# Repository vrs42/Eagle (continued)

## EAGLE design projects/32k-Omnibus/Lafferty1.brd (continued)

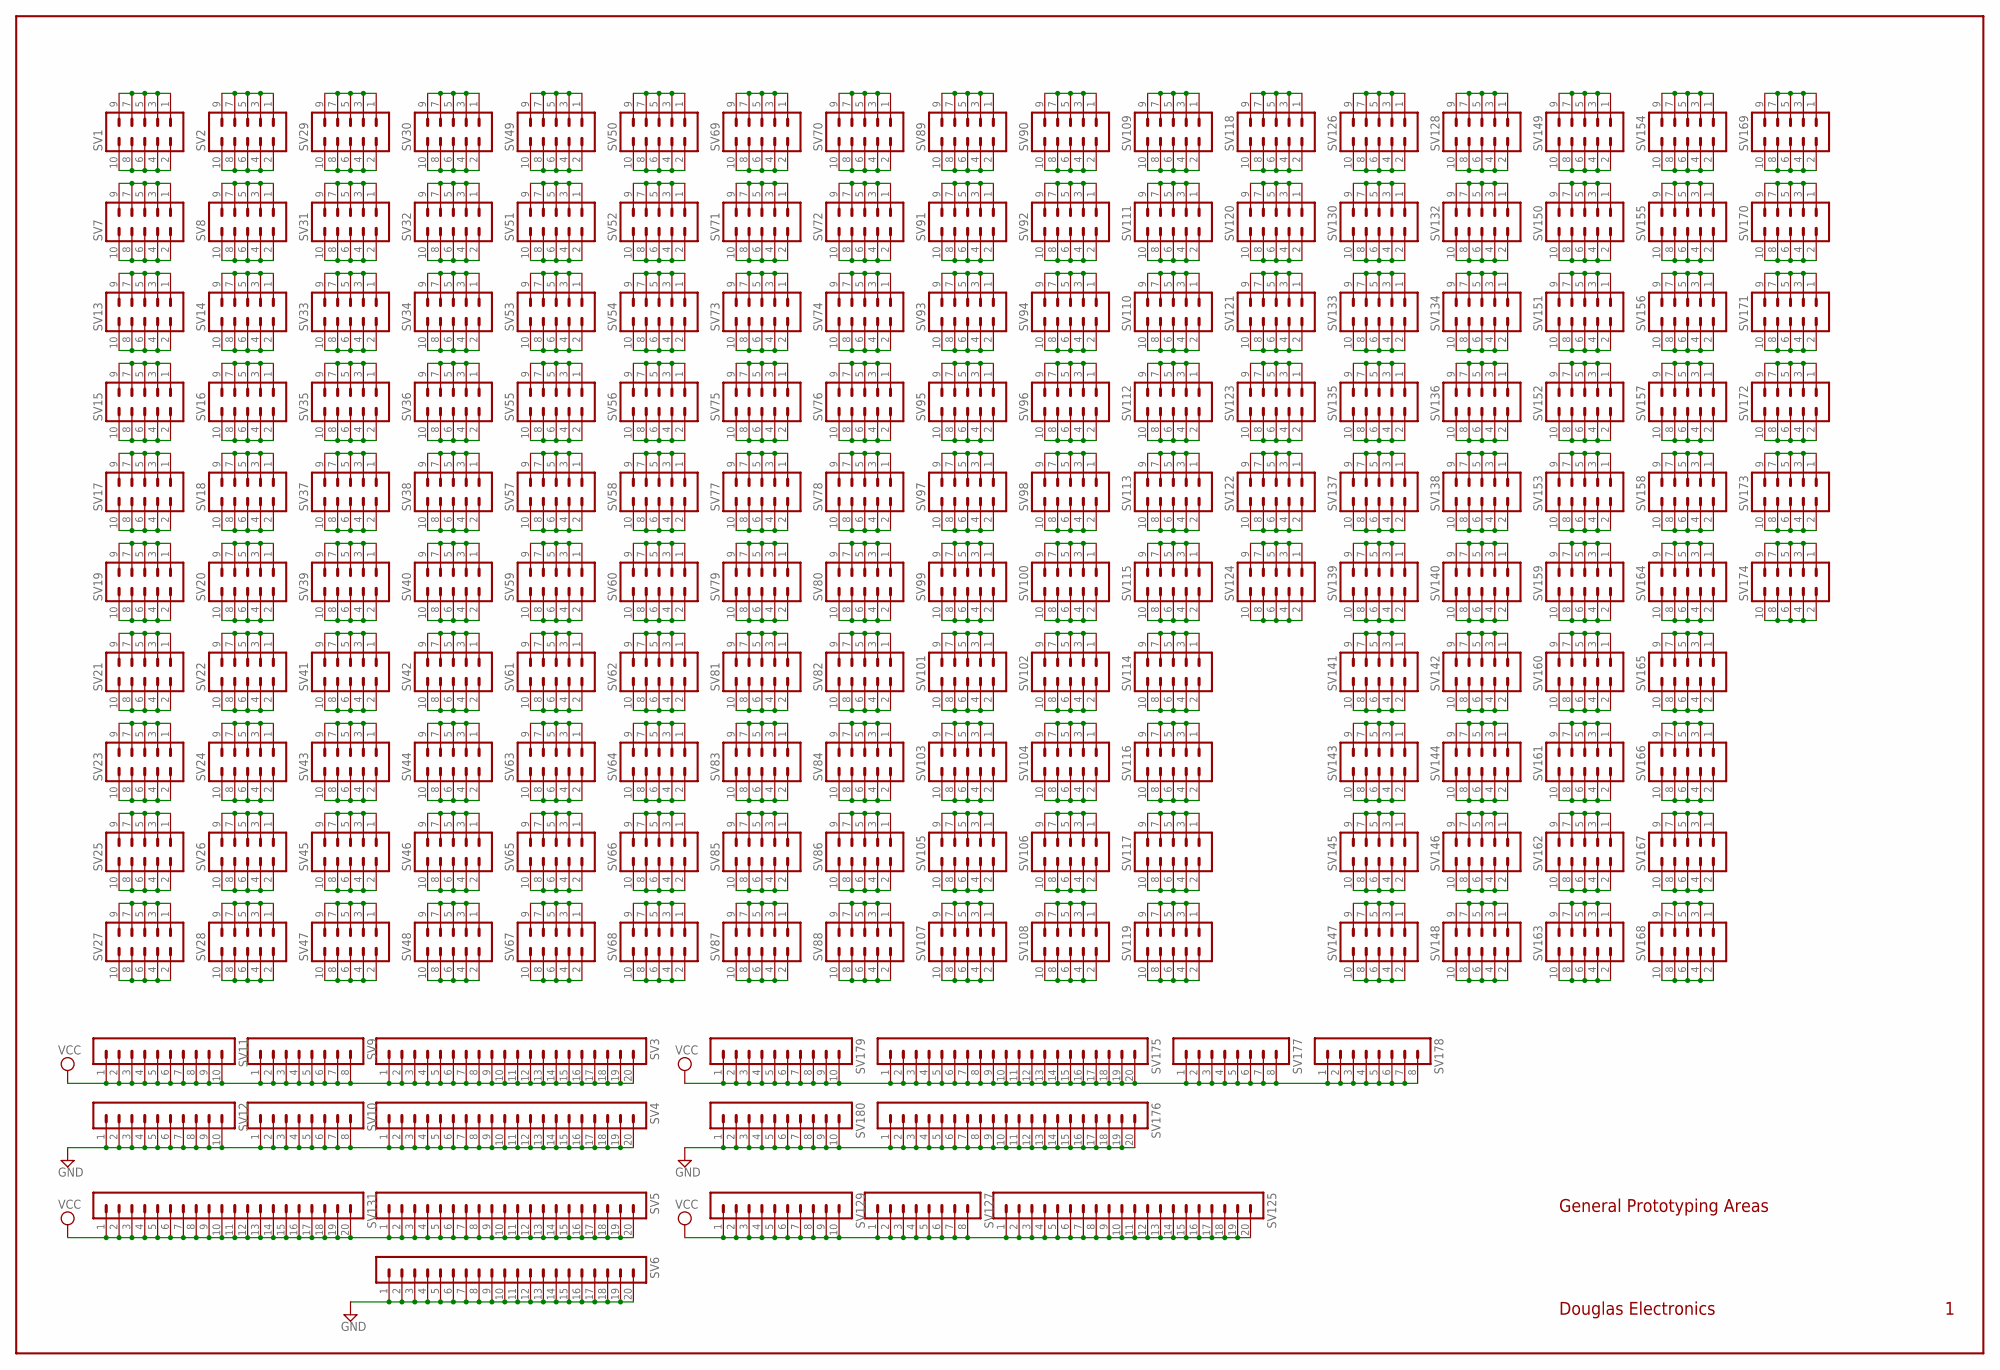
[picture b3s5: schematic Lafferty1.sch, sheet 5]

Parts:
SV1, SV2, SV7, SV8, SV13, SV14, SV15, SV16, SV17, SV18, SV19, SV20, SV21, SV22, SV23, SV24, SV25, SV26, SV27, SV28, SV29, SV30, SV31, SV32, SV33, SV34, SV35, SV36, SV37, SV38, SV39, SV40, SV41, SV42, SV43, SV44, SV45, SV46, SV47, SV48, SV49, SV50, SV51, SV52, SV53, SV54, SV55, SV56, SV57, SV58, SV59, SV60, SV61, SV62, SV63, SV64, SV65, SV66, SV67, SV68, SV69, SV70, SV71, SV72, SV73, SV74, SV75, SV76, SV77, SV78, SV79, SV80, SV81, SV82, SV83, SV84, SV85, SV86, SV87, SV88, SV89, SV90, SV91, SV92, SV93, SV94, SV95, SV96, SV97, SV98, SV99, SV100, SV101, SV102, SV103, SV104, SV105, SV106, SV107, SV108, SV109, SV110, SV111, SV112, SV113, SV114, SV115, SV116, SV117, SV118, SV119, SV120, SV121, SV122, SV123, SV124, SV126, SV128, SV130, SV132, SV133, SV134, SV135, SV136, SV137, SV138, SV139, SV140, SV141, SV142, SV143, SV144, SV145, SV146, SV147, SV148, SV149, SV150, SV151, SV152, SV153, SV154, SV155, SV156, SV157, SV158, SV159, SV160, SV161, SV162, SV163, SV164, SV165, SV166, SV167, SV168, SV169, SV170, SV171, SV172, SV173, SV174: MA05-2
SV3, SV4, SV5, SV6, SV125, SV131, SV175, SV176: MA20-1
SV9, SV10, SV127, SV177, SV178: MA08-1
SV11, SV12, SV129, SV179, SV180: MA10-1

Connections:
GND: SV4.1, SV4.2, SV4.3, SV4.4, SV4.5, SV4.6, SV4.7, SV4.8, SV4.9, SV4.10, SV4.11, SV4.12, SV4.13, SV4.14, SV4.15, SV4.16, SV4.17, SV4.18, SV4.19, SV4.20, SV6.1, SV6.2, SV6.3, SV6.4, SV6.5, SV6.6, SV6.7, SV6.8, SV6.9, SV6.10, SV6.11, SV6.12, SV6.13, SV6.14, SV6.15, SV6.16, SV6.17, SV6.18, SV6.19, SV6.20, SV10.1, SV10.2, SV10.3, SV10.4, SV10.5, SV10.6, SV10.7, SV10.8, SV12.1, SV12.2, SV12.3, SV12.4, SV12.5, SV12.6, SV12.7, SV12.8, SV12.9, SV12.10, SV176.1, SV176.2, SV176.3, SV176.4, SV176.5, SV176.6, SV176.7, SV176.8, SV176.9, SV176.10, SV176.11, SV176.12, SV176.13, SV176.14, SV176.15, SV176.16, SV176.17, SV176.18, SV176.19, SV176.20, SV180.1, SV180.2, SV180.3, SV180.4, SV180.5, SV180.6, SV180.7, SV180.8, SV180.9, SV180.10; also elsewhere on the board
unnamed: SV1.1, SV1.3, SV1.5, SV1.7, SV1.9
unnamed: SV1.2, SV1.4, SV1.6, SV1.8, SV1.10
unnamed: SV7.1, SV7.3, SV7.5, SV7.7, SV7.9
unnamed: SV2.1, SV2.3, SV2.5, SV2.7, SV2.9
unnamed: SV2.2, SV2.4, SV2.6, SV2.8, SV2.10
unnamed: SV7.2, SV7.4, SV7.6, SV7.8, SV7.10
unnamed: SV8.1, SV8.3, SV8.5, SV8.7, SV8.9
unnamed: SV8.2, SV8.4, SV8.6, SV8.8, SV8.10
unnamed: SV13.1, SV13.3, SV13.5, SV13.7, SV13.9
unnamed: SV13.2, SV13.4, SV13.6, SV13.8, SV13.10
unnamed: SV14.1, SV14.3, SV14.5, SV14.7, SV14.9
unnamed: SV14.2, SV14.4, SV14.6, SV14.8, SV14.10
unnamed: SV15.1, SV15.3, SV15.5, SV15.7, SV15.9
unnamed: SV15.2, SV15.4, SV15.6, SV15.8, SV15.10
unnamed: SV16.1, SV16.3, SV16.5, SV16.7, SV16.9
unnamed: SV16.2, SV16.4, SV16.6, SV16.8, SV16.10
unnamed: SV17.1, SV17.3, SV17.5, SV17.7, SV17.9
unnamed: SV17.2, SV17.4, SV17.6, SV17.8, SV17.10
unnamed: SV18.1, SV18.3, SV18.5, SV18.7, SV18.9
unnamed: SV18.2, SV18.4, SV18.6, SV18.8, SV18.10
unnamed: SV19.1, SV19.3, SV19.5, SV19.7, SV19.9
unnamed: SV19.2, SV19.4, SV19.6, SV19.8, SV19.10
unnamed: SV20.1, SV20.3, SV20.5, SV20.7, SV20.9
unnamed: SV20.2, SV20.4, SV20.6, SV20.8, SV20.10
unnamed: SV21.1, SV21.3, SV21.5, SV21.7, SV21.9
unnamed: SV21.2, SV21.4, SV21.6, SV21.8, SV21.10
unnamed: SV22.1, SV22.3, SV22.5, SV22.7, SV22.9
unnamed: SV22.2, SV22.4, SV22.6, SV22.8, SV22.10
unnamed: SV23.1, SV23.3, SV23.5, SV23.7, SV23.9
unnamed: SV23.2, SV23.4, SV23.6, SV23.8, SV23.10
unnamed: SV24.1, SV24.3, SV24.5, SV24.7, SV24.9
unnamed: SV24.2, SV24.4, SV24.6, SV24.8, SV24.10
unnamed: SV25.1, SV25.3, SV25.5, SV25.7, SV25.9
unnamed: SV25.2, SV25.4, SV25.6, SV25.8, SV25.10
unnamed: SV26.1, SV26.3, SV26.5, SV26.7, SV26.9
unnamed: SV26.2, SV26.4, SV26.6, SV26.8, SV26.10
unnamed: SV27.1, SV27.3, SV27.5, SV27.7, SV27.9
unnamed: SV27.2, SV27.4, SV27.6, SV27.8, SV27.10
unnamed: SV28.1, SV28.3, SV28.5, SV28.7, SV28.9
unnamed: SV28.2, SV28.4, SV28.6, SV28.8, SV28.10
unnamed: SV29.1, SV29.3, SV29.5, SV29.7, SV29.9
unnamed: SV29.2, SV29.4, SV29.6, SV29.8, SV29.10
unnamed: SV30.1, SV30.3, SV30.5, SV30.7, SV30.9
unnamed: SV30.2, SV30.4, SV30.6, SV30.8, SV30.10
unnamed: SV31.1, SV31.3, SV31.5, SV31.7, SV31.9
unnamed: SV31.2, SV31.4, SV31.6, SV31.8, SV31.10
unnamed: SV32.1, SV32.3, SV32.5, SV32.7, SV32.9
unnamed: SV32.2, SV32.4, SV32.6, SV32.8, SV32.10
unnamed: SV33.1, SV33.3, SV33.5, SV33.7, SV33.9
unnamed: SV33.2, SV33.4, SV33.6, SV33.8, SV33.10
unnamed: SV34.1, SV34.3, SV34.5, SV34.7, SV34.9
unnamed: SV34.2, SV34.4, SV34.6, SV34.8, SV34.10
unnamed: SV35.1, SV35.3, SV35.5, SV35.7, SV35.9
unnamed: SV35.2, SV35.4, SV35.6, SV35.8, SV35.10
unnamed: SV36.1, SV36.3, SV36.5, SV36.7, SV36.9
unnamed: SV36.2, SV36.4, SV36.6, SV36.8, SV36.10
unnamed: SV37.1, SV37.3, SV37.5, SV37.7, SV37.9
unnamed: SV37.2, SV37.4, SV37.6, SV37.8, SV37.10
unnamed: SV38.1, SV38.3, SV38.5, SV38.7, SV38.9
unnamed: SV38.2, SV38.4, SV38.6, SV38.8, SV38.10
unnamed: SV39.1, SV39.3, SV39.5, SV39.7, SV39.9
unnamed: SV39.2, SV39.4, SV39.6, SV39.8, SV39.10
unnamed: SV40.1, SV40.3, SV40.5, SV40.7, SV40.9
unnamed: SV40.2, SV40.4, SV40.6, SV40.8, SV40.10
unnamed: SV41.1, SV41.3, SV41.5, SV41.7, SV41.9
unnamed: SV41.2, SV41.4, SV41.6, SV41.8, SV41.10
unnamed: SV42.1, SV42.3, SV42.5, SV42.7, SV42.9
unnamed: SV42.2, SV42.4, SV42.6, SV42.8, SV42.10
unnamed: SV43.1, SV43.3, SV43.5, SV43.7, SV43.9
unnamed: SV43.2, SV43.4, SV43.6, SV43.8, SV43.10
unnamed: SV44.1, SV44.3, SV44.5, SV44.7, SV44.9
unnamed: SV44.2, SV44.4, SV44.6, SV44.8, SV44.10
unnamed: SV45.1, SV45.3, SV45.5, SV45.7, SV45.9
unnamed: SV45.2, SV45.4, SV45.6, SV45.8, SV45.10
unnamed: SV46.1, SV46.3, SV46.5, SV46.7, SV46.9
unnamed: SV46.2, SV46.4, SV46.6, SV46.8, SV46.10
unnamed: SV47.1, SV47.3, SV47.5, SV47.7, SV47.9
unnamed: SV47.2, SV47.4, SV47.6, SV47.8, SV47.10
unnamed: SV48.1, SV48.3, SV48.5, SV48.7, SV48.9
unnamed: SV48.2, SV48.4, SV48.6, SV48.8, SV48.10
unnamed: SV49.1, SV49.3, SV49.5, SV49.7, SV49.9
unnamed: SV49.2, SV49.4, SV49.6, SV49.8, SV49.10
unnamed: SV50.1, SV50.3, SV50.5, SV50.7, SV50.9
unnamed: SV50.2, SV50.4, SV50.6, SV50.8, SV50.10
unnamed: SV51.1, SV51.3, SV51.5, SV51.7, SV51.9
unnamed: SV51.2, SV51.4, SV51.6, SV51.8, SV51.10
unnamed: SV52.1, SV52.3, SV52.5, SV52.7, SV52.9
unnamed: SV52.2, SV52.4, SV52.6, SV52.8, SV52.10
unnamed: SV53.1, SV53.3, SV53.5, SV53.7, SV53.9
unnamed: SV53.2, SV53.4, SV53.6, SV53.8, SV53.10
unnamed: SV54.1, SV54.3, SV54.5, SV54.7, SV54.9
unnamed: SV54.2, SV54.4, SV54.6, SV54.8, SV54.10
unnamed: SV55.1, SV55.3, SV55.5, SV55.7, SV55.9
unnamed: SV55.2, SV55.4, SV55.6, SV55.8, SV55.10
unnamed: SV56.1, SV56.3, SV56.5, SV56.7, SV56.9
unnamed: SV56.2, SV56.4, SV56.6, SV56.8, SV56.10
unnamed: SV57.1, SV57.3, SV57.5, SV57.7, SV57.9
unnamed: SV57.2, SV57.4, SV57.6, SV57.8, SV57.10
unnamed: SV58.1, SV58.3, SV58.5, SV58.7, SV58.9
unnamed: SV58.2, SV58.4, SV58.6, SV58.8, SV58.10
unnamed: SV59.1, SV59.3, SV59.5, SV59.7, SV59.9
unnamed: SV59.2, SV59.4, SV59.6, SV59.8, SV59.10
unnamed: SV60.1, SV60.3, SV60.5, SV60.7, SV60.9
unnamed: SV60.2, SV60.4, SV60.6, SV60.8, SV60.10
unnamed: SV61.1, SV61.3, SV61.5, SV61.7, SV61.9
unnamed: SV61.2, SV61.4, SV61.6, SV61.8, SV61.10
unnamed: SV62.1, SV62.3, SV62.5, SV62.7, SV62.9
unnamed: SV62.2, SV62.4, SV62.6, SV62.8, SV62.10
unnamed: SV63.1, SV63.3, SV63.5, SV63.7, SV63.9
unnamed: SV63.2, SV63.4, SV63.6, SV63.8, SV63.10
unnamed: SV64.1, SV64.3, SV64.5, SV64.7, SV64.9
unnamed: SV64.2, SV64.4, SV64.6, SV64.8, SV64.10
unnamed: SV65.1, SV65.3, SV65.5, SV65.7, SV65.9
unnamed: SV65.2, SV65.4, SV65.6, SV65.8, SV65.10
unnamed: SV66.1, SV66.3, SV66.5, SV66.7, SV66.9
unnamed: SV66.2, SV66.4, SV66.6, SV66.8, SV66.10
unnamed: SV67.1, SV67.3, SV67.5, SV67.7, SV67.9
unnamed: SV67.2, SV67.4, SV67.6, SV67.8, SV67.10
unnamed: SV68.1, SV68.3, SV68.5, SV68.7, SV68.9
unnamed: SV68.2, SV68.4, SV68.6, SV68.8, SV68.10
unnamed: SV69.1, SV69.3, SV69.5, SV69.7, SV69.9
unnamed: SV69.2, SV69.4, SV69.6, SV69.8, SV69.10
unnamed: SV70.1, SV70.3, SV70.5, SV70.7, SV70.9
unnamed: SV70.2, SV70.4, SV70.6, SV70.8, SV70.10
unnamed: SV71.1, SV71.3, SV71.5, SV71.7, SV71.9
unnamed: SV71.2, SV71.4, SV71.6, SV71.8, SV71.10
unnamed: SV72.1, SV72.3, SV72.5, SV72.7, SV72.9
unnamed: SV72.2, SV72.4, SV72.6, SV72.8, SV72.10
unnamed: SV73.1, SV73.3, SV73.5, SV73.7, SV73.9
unnamed: SV73.2, SV73.4, SV73.6, SV73.8, SV73.10
unnamed: SV74.1, SV74.3, SV74.5, SV74.7, SV74.9
unnamed: SV74.2, SV74.4, SV74.6, SV74.8, SV74.10
unnamed: SV75.1, SV75.3, SV75.5, SV75.7, SV75.9
unnamed: SV75.2, SV75.4, SV75.6, SV75.8, SV75.10
unnamed: SV76.1, SV76.3, SV76.5, SV76.7, SV76.9
unnamed: SV76.2, SV76.4, SV76.6, SV76.8, SV76.10
unnamed: SV77.1, SV77.3, SV77.5, SV77.7, SV77.9
unnamed: SV77.2, SV77.4, SV77.6, SV77.8, SV77.10
unnamed: SV78.1, SV78.3, SV78.5, SV78.7, SV78.9
unnamed: SV78.2, SV78.4, SV78.6, SV78.8, SV78.10
unnamed: SV79.1, SV79.3, SV79.5, SV79.7, SV79.9
unnamed: SV79.2, SV79.4, SV79.6, SV79.8, SV79.10
unnamed: SV80.1, SV80.3, SV80.5, SV80.7, SV80.9
unnamed: SV80.2, SV80.4, SV80.6, SV80.8, SV80.10
unnamed: SV81.1, SV81.3, SV81.5, SV81.7, SV81.9
unnamed: SV81.2, SV81.4, SV81.6, SV81.8, SV81.10
unnamed: SV82.1, SV82.3, SV82.5, SV82.7, SV82.9
unnamed: SV82.2, SV82.4, SV82.6, SV82.8, SV82.10
unnamed: SV83.1, SV83.3, SV83.5, SV83.7, SV83.9
unnamed: SV83.2, SV83.4, SV83.6, SV83.8, SV83.10
unnamed: SV84.1, SV84.3, SV84.5, SV84.7, SV84.9
unnamed: SV84.2, SV84.4, SV84.6, SV84.8, SV84.10
unnamed: SV85.1, SV85.3, SV85.5, SV85.7, SV85.9
unnamed: SV85.2, SV85.4, SV85.6, SV85.8, SV85.10
unnamed: SV86.1, SV86.3, SV86.5, SV86.7, SV86.9
unnamed: SV86.2, SV86.4, SV86.6, SV86.8, SV86.10
unnamed: SV87.1, SV87.3, SV87.5, SV87.7, SV87.9
unnamed: SV87.2, SV87.4, SV87.6, SV87.8, SV87.10
unnamed: SV88.1, SV88.3, SV88.5, SV88.7, SV88.9
unnamed: SV88.2, SV88.4, SV88.6, SV88.8, SV88.10
unnamed: SV89.1, SV89.3, SV89.5, SV89.7, SV89.9
unnamed: SV89.2, SV89.4, SV89.6, SV89.8, SV89.10
unnamed: SV90.1, SV90.3, SV90.5, SV90.7, SV90.9
unnamed: SV90.2, SV90.4, SV90.6, SV90.8, SV90.10
unnamed: SV91.1, SV91.3, SV91.5, SV91.7, SV91.9
unnamed: SV91.2, SV91.4, SV91.6, SV91.8, SV91.10
unnamed: SV92.1, SV92.3, SV92.5, SV92.7, SV92.9
unnamed: SV92.2, SV92.4, SV92.6, SV92.8, SV92.10
unnamed: SV93.1, SV93.3, SV93.5, SV93.7, SV93.9
unnamed: SV93.2, SV93.4, SV93.6, SV93.8, SV93.10
unnamed: SV94.1, SV94.3, SV94.5, SV94.7, SV94.9
unnamed: SV94.2, SV94.4, SV94.6, SV94.8, SV94.10
unnamed: SV95.1, SV95.3, SV95.5, SV95.7, SV95.9
unnamed: SV95.2, SV95.4, SV95.6, SV95.8, SV95.10
unnamed: SV96.1, SV96.3, SV96.5, SV96.7, SV96.9
unnamed: SV96.2, SV96.4, SV96.6, SV96.8, SV96.10
unnamed: SV97.1, SV97.3, SV97.5, SV97.7, SV97.9
unnamed: SV97.2, SV97.4, SV97.6, SV97.8, SV97.10
unnamed: SV98.1, SV98.3, SV98.5, SV98.7, SV98.9
unnamed: SV98.2, SV98.4, SV98.6, SV98.8, SV98.10
unnamed: SV99.1, SV99.3, SV99.5, SV99.7, SV99.9
unnamed: SV99.2, SV99.4, SV99.6, SV99.8, SV99.10
unnamed: SV100.1, SV100.3, SV100.5, SV100.7, SV100.9
unnamed: SV100.2, SV100.4, SV100.6, SV100.8, SV100.10
unnamed: SV101.1, SV101.3, SV101.5, SV101.7, SV101.9
unnamed: SV101.2, SV101.4, SV101.6, SV101.8, SV101.10
unnamed: SV102.1, SV102.3, SV102.5, SV102.7, SV102.9
unnamed: SV102.2, SV102.4, SV102.6, SV102.8, SV102.10
unnamed: SV103.1, SV103.3, SV103.5, SV103.7, SV103.9
unnamed: SV103.2, SV103.4, SV103.6, SV103.8, SV103.10
unnamed: SV104.1, SV104.3, SV104.5, SV104.7, SV104.9
unnamed: SV104.2, SV104.4, SV104.6, SV104.8, SV104.10
unnamed: SV105.1, SV105.3, SV105.5, SV105.7, SV105.9
unnamed: SV105.2, SV105.4, SV105.6, SV105.8, SV105.10
unnamed: SV106.1, SV106.3, SV106.5, SV106.7, SV106.9
unnamed: SV106.2, SV106.4, SV106.6, SV106.8, SV106.10
unnamed: SV107.1, SV107.3, SV107.5, SV107.7, SV107.9
unnamed: SV107.2, SV107.4, SV107.6, SV107.8, SV107.10
unnamed: SV108.1, SV108.3, SV108.5, SV108.7, SV108.9
unnamed: SV108.2, SV108.4, SV108.6, SV108.8, SV108.10
unnamed: SV109.1, SV109.3, SV109.5, SV109.7, SV109.9
unnamed: SV109.2, SV109.4, SV109.6, SV109.8, SV109.10
unnamed: SV110.1, SV110.3, SV110.5, SV110.7, SV110.9
unnamed: SV110.2, SV110.4, SV110.6, SV110.8, SV110.10
unnamed: SV111.1, SV111.3, SV111.5, SV111.7, SV111.9
unnamed: SV111.2, SV111.4, SV111.6, SV111.8, SV111.10
unnamed: SV112.1, SV112.3, SV112.5, SV112.7, SV112.9
unnamed: SV112.2, SV112.4, SV112.6, SV112.8, SV112.10
unnamed: SV113.1, SV113.3, SV113.5, SV113.7, SV113.9
unnamed: SV113.2, SV113.4, SV113.6, SV113.8, SV113.10
unnamed: SV114.1, SV114.3, SV114.5, SV114.7, SV114.9
unnamed: SV114.2, SV114.4, SV114.6, SV114.8, SV114.10
unnamed: SV115.1, SV115.3, SV115.5, SV115.7, SV115.9
unnamed: SV115.2, SV115.4, SV115.6, SV115.8, SV115.10
unnamed: SV116.1, SV116.3, SV116.5, SV116.7, SV116.9
unnamed: SV116.2, SV116.4, SV116.6, SV116.8, SV116.10
unnamed: SV117.1, SV117.3, SV117.5, SV117.7, SV117.9
unnamed: SV117.2, SV117.4, SV117.6, SV117.8, SV117.10
unnamed: SV118.1, SV118.3, SV118.5, SV118.7, SV118.9
unnamed: SV118.2, SV118.4, SV118.6, SV118.8, SV118.10
unnamed: SV119.1, SV119.3, SV119.5, SV119.7, SV119.9
unnamed: SV119.2, SV119.4, SV119.6, SV119.8, SV119.10
unnamed: SV120.1, SV120.3, SV120.5, SV120.7, SV120.9
unnamed: SV120.2, SV120.4, SV120.6, SV120.8, SV120.10
unnamed: SV121.1, SV121.3, SV121.5, SV121.7, SV121.9
unnamed: SV121.2, SV121.4, SV121.6, SV121.8, SV121.10
unnamed: SV122.1, SV122.3, SV122.5, SV122.7, SV122.9
unnamed: SV122.2, SV122.4, SV122.6, SV122.8, SV122.10
unnamed: SV123.1, SV123.3, SV123.5, SV123.7, SV123.9
unnamed: SV123.2, SV123.4, SV123.6, SV123.8, SV123.10
unnamed: SV124.1, SV124.3, SV124.5, SV124.7, SV124.9
unnamed: SV124.2, SV124.4, SV124.6, SV124.8, SV124.10
unnamed: SV126.1, SV126.3, SV126.5, SV126.7, SV126.9
unnamed: SV126.2, SV126.4, SV126.6, SV126.8, SV126.10
unnamed: SV128.1, SV128.3, SV128.5, SV128.7, SV128.9
unnamed: SV128.2, SV128.4, SV128.6, SV128.8, SV128.10
unnamed: SV130.1, SV130.3, SV130.5, SV130.7, SV130.9
unnamed: SV130.2, SV130.4, SV130.6, SV130.8, SV130.10
unnamed: SV132.1, SV132.3, SV132.5, SV132.7, SV132.9
unnamed: SV132.2, SV132.4, SV132.6, SV132.8, SV132.10
unnamed: SV133.1, SV133.3, SV133.5, SV133.7, SV133.9
unnamed: SV133.2, SV133.4, SV133.6, SV133.8, SV133.10
unnamed: SV134.1, SV134.3, SV134.5, SV134.7, SV134.9
unnamed: SV134.2, SV134.4, SV134.6, SV134.8, SV134.10
unnamed: SV135.1, SV135.3, SV135.5, SV135.7, SV135.9
unnamed: SV135.2, SV135.4, SV135.6, SV135.8, SV135.10
unnamed: SV136.1, SV136.3, SV136.5, SV136.7, SV136.9
unnamed: SV136.2, SV136.4, SV136.6, SV136.8, SV136.10
unnamed: SV137.1, SV137.3, SV137.5, SV137.7, SV137.9
unnamed: SV137.2, SV137.4, SV137.6, SV137.8, SV137.10
unnamed: SV138.1, SV138.3, SV138.5, SV138.7, SV138.9
unnamed: SV138.2, SV138.4, SV138.6, SV138.8, SV138.10
unnamed: SV139.1, SV139.3, SV139.5, SV139.7, SV139.9
unnamed: SV139.2, SV139.4, SV139.6, SV139.8, SV139.10
unnamed: SV140.1, SV140.3, SV140.5, SV140.7, SV140.9
unnamed: SV140.2, SV140.4, SV140.6, SV140.8, SV140.10
unnamed: SV141.1, SV141.3, SV141.5, SV141.7, SV141.9
unnamed: SV141.2, SV141.4, SV141.6, SV141.8, SV141.10
unnamed: SV142.1, SV142.3, SV142.5, SV142.7, SV142.9
unnamed: SV142.2, SV142.4, SV142.6, SV142.8, SV142.10
unnamed: SV143.1, SV143.3, SV143.5, SV143.7, SV143.9
unnamed: SV143.2, SV143.4, SV143.6, SV143.8, SV143.10
unnamed: SV144.1, SV144.3, SV144.5, SV144.7, SV144.9
unnamed: SV144.2, SV144.4, SV144.6, SV144.8, SV144.10
unnamed: SV145.1, SV145.3, SV145.5, SV145.7, SV145.9
unnamed: SV145.2, SV145.4, SV145.6, SV145.8, SV145.10
unnamed: SV146.1, SV146.3, SV146.5, SV146.7, SV146.9
unnamed: SV146.2, SV146.4, SV146.6, SV146.8, SV146.10
unnamed: SV147.1, SV147.3, SV147.5, SV147.7, SV147.9
unnamed: SV147.2, SV147.4, SV147.6, SV147.8, SV147.10
unnamed: SV148.1, SV148.3, SV148.5, SV148.7, SV148.9
unnamed: SV148.2, SV148.4, SV148.6, SV148.8, SV148.10
unnamed: SV149.1, SV149.3, SV149.5, SV149.7, SV149.9
unnamed: SV149.2, SV149.4, SV149.6, SV149.8, SV149.10
unnamed: SV150.1, SV150.3, SV150.5, SV150.7, SV150.9
unnamed: SV150.2, SV150.4, SV150.6, SV150.8, SV150.10
unnamed: SV151.1, SV151.3, SV151.5, SV151.7, SV151.9
unnamed: SV151.2, SV151.4, SV151.6, SV151.8, SV151.10
unnamed: SV152.1, SV152.3, SV152.5, SV152.7, SV152.9
unnamed: SV152.2, SV152.4, SV152.6, SV152.8, SV152.10
unnamed: SV153.1, SV153.3, SV153.5, SV153.7, SV153.9
unnamed: SV153.2, SV153.4, SV153.6, SV153.8, SV153.10
unnamed: SV154.1, SV154.3, SV154.5, SV154.7, SV154.9
unnamed: SV154.2, SV154.4, SV154.6, SV154.8, SV154.10
unnamed: SV155.1, SV155.3, SV155.5, SV155.7, SV155.9
unnamed: SV155.2, SV155.4, SV155.6, SV155.8, SV155.10
unnamed: SV156.1, SV156.3, SV156.5, SV156.7, SV156.9
unnamed: SV156.2, SV156.4, SV156.6, SV156.8, SV156.10
unnamed: SV157.1, SV157.3, SV157.5, SV157.7, SV157.9
unnamed: SV157.2, SV157.4, SV157.6, SV157.8, SV157.10
unnamed: SV158.1, SV158.3, SV158.5, SV158.7, SV158.9
unnamed: SV158.2, SV158.4, SV158.6, SV158.8, SV158.10
unnamed: SV159.1, SV159.3, SV159.5, SV159.7, SV159.9
unnamed: SV159.2, SV159.4, SV159.6, SV159.8, SV159.10
unnamed: SV160.1, SV160.3, SV160.5, SV160.7, SV160.9
unnamed: SV160.2, SV160.4, SV160.6, SV160.8, SV160.10
unnamed: SV161.1, SV161.3, SV161.5, SV161.7, SV161.9
unnamed: SV161.2, SV161.4, SV161.6, SV161.8, SV161.10
unnamed: SV162.1, SV162.3, SV162.5, SV162.7, SV162.9
unnamed: SV162.2, SV162.4, SV162.6, SV162.8, SV162.10
unnamed: SV163.1, SV163.3, SV163.5, SV163.7, SV163.9
unnamed: SV163.2, SV163.4, SV163.6, SV163.8, SV163.10
unnamed: SV164.1, SV164.3, SV164.5, SV164.7, SV164.9
unnamed: SV164.2, SV164.4, SV164.6, SV164.8, SV164.10
unnamed: SV165.1, SV165.3, SV165.5, SV165.7, SV165.9
unnamed: SV165.2, SV165.4, SV165.6, SV165.8, SV165.10
unnamed: SV166.1, SV166.3, SV166.5, SV166.7, SV166.9
unnamed: SV166.2, SV166.4, SV166.6, SV166.8, SV166.10
unnamed: SV167.1, SV167.3, SV167.5, SV167.7, SV167.9
unnamed: SV167.2, SV167.4, SV167.6, SV167.8, SV167.10
unnamed: SV168.1, SV168.3, SV168.5, SV168.7, SV168.9
unnamed: SV168.2, SV168.4, SV168.6, SV168.8, SV168.10
unnamed: SV169.1, SV169.3, SV169.5, SV169.7, SV169.9
unnamed: SV169.2, SV169.4, SV169.6, SV169.8, SV169.10
unnamed: SV170.1, SV170.3, SV170.5, SV170.7, SV170.9
unnamed: SV170.2, SV170.4, SV170.6, SV170.8, SV170.10
unnamed: SV171.1, SV171.3, SV171.5, SV171.7, SV171.9
unnamed: SV171.2, SV171.4, SV171.6, SV171.8, SV171.10
unnamed: SV172.1, SV172.3, SV172.5, SV172.7, SV172.9
unnamed: SV172.2, SV172.4, SV172.6, SV172.8, SV172.10
unnamed: SV173.1, SV173.3, SV173.5, SV173.7, SV173.9
unnamed: SV173.2, SV173.4, SV173.6, SV173.8, SV173.10
unnamed: SV174.1, SV174.3, SV174.5, SV174.7, SV174.9
unnamed: SV174.2, SV174.4, SV174.6, SV174.8, SV174.10
VCC: SV3.1, SV3.2, SV3.3, SV3.4, SV3.5, SV3.6, SV3.7, SV3.8, SV3.9, SV3.10, SV3.11, SV3.12, SV3.13, SV3.14, SV3.15, SV3.16, SV3.17, SV3.18, SV3.19, SV3.20, SV5.1, SV5.2, SV5.3, SV5.4, SV5.5, SV5.6, SV5.7, SV5.8, SV5.9, SV5.10, SV5.11, SV5.12, SV5.13, SV5.14, SV5.15, SV5.16, SV5.17, SV5.18, SV5.19, SV5.20, SV9.1, SV9.2, SV9.3, SV9.4, SV9.5, SV9.6, SV9.7, SV9.8, SV11.1, SV11.2, SV11.3, SV11.4, SV11.5, SV11.6, SV11.7, SV11.8, SV11.9, SV11.10, SV125.1, SV125.2, SV125.3, SV125.4, SV125.5, SV125.6, SV125.7, SV125.8, SV125.9, SV125.10, SV125.11, SV125.12, SV125.13, SV125.14, SV125.15, SV125.16, SV125.17, SV125.18, SV125.19, SV125.20, SV127.1, SV127.2, SV127.3, SV127.4, SV127.5, SV127.6, SV127.7, SV127.8, SV129.1, SV129.2, SV129.3, SV129.4, SV129.5, SV129.6, SV129.7, SV129.8, SV129.9, SV129.10, SV131.1, SV131.2, SV131.3, SV131.4, SV131.5, SV131.6, SV131.7, SV131.8, SV131.9, SV131.10, SV131.11, SV131.12, SV131.13, SV131.14, SV131.15, SV131.16, SV131.17, SV131.18, SV131.19, SV131.20, SV175.1, SV175.2, SV175.3, SV175.4, SV175.5, SV175.6, SV175.7, SV175.8, SV175.9, SV175.10, SV175.11, SV175.12, SV175.13, SV175.14, SV175.15, SV175.16, SV175.17, SV175.18, SV175.19, SV175.20, SV177.1, SV177.2, SV177.3, SV177.4, SV177.5, SV177.6, SV177.7, SV177.8, SV178.1, SV178.2, SV178.3, SV178.4, SV178.5, SV178.6, SV178.7, SV178.8, SV179.1, SV179.2, SV179.3, SV179.4, SV179.5, SV179.6, SV179.7, SV179.8, SV179.9, SV179.10; also elsewhere on the board

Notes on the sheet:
General Prototyping Areas
Douglas Electronics

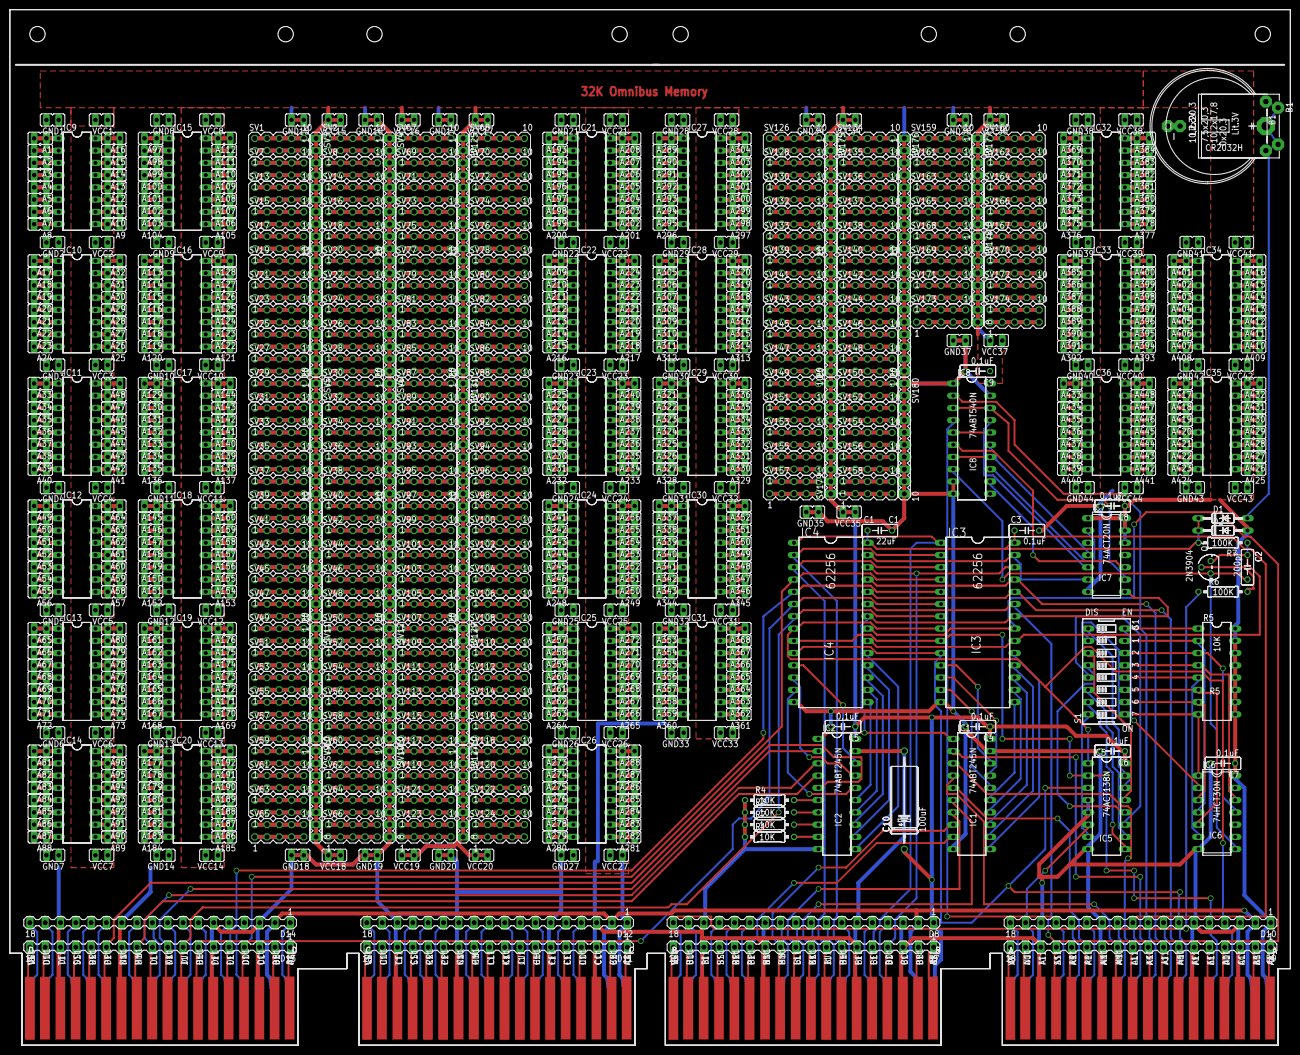
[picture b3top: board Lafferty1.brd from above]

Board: 2 copper layers, 265.4 x 214.6 mm, 784 parts (0 on the bottom side), 930 nets.

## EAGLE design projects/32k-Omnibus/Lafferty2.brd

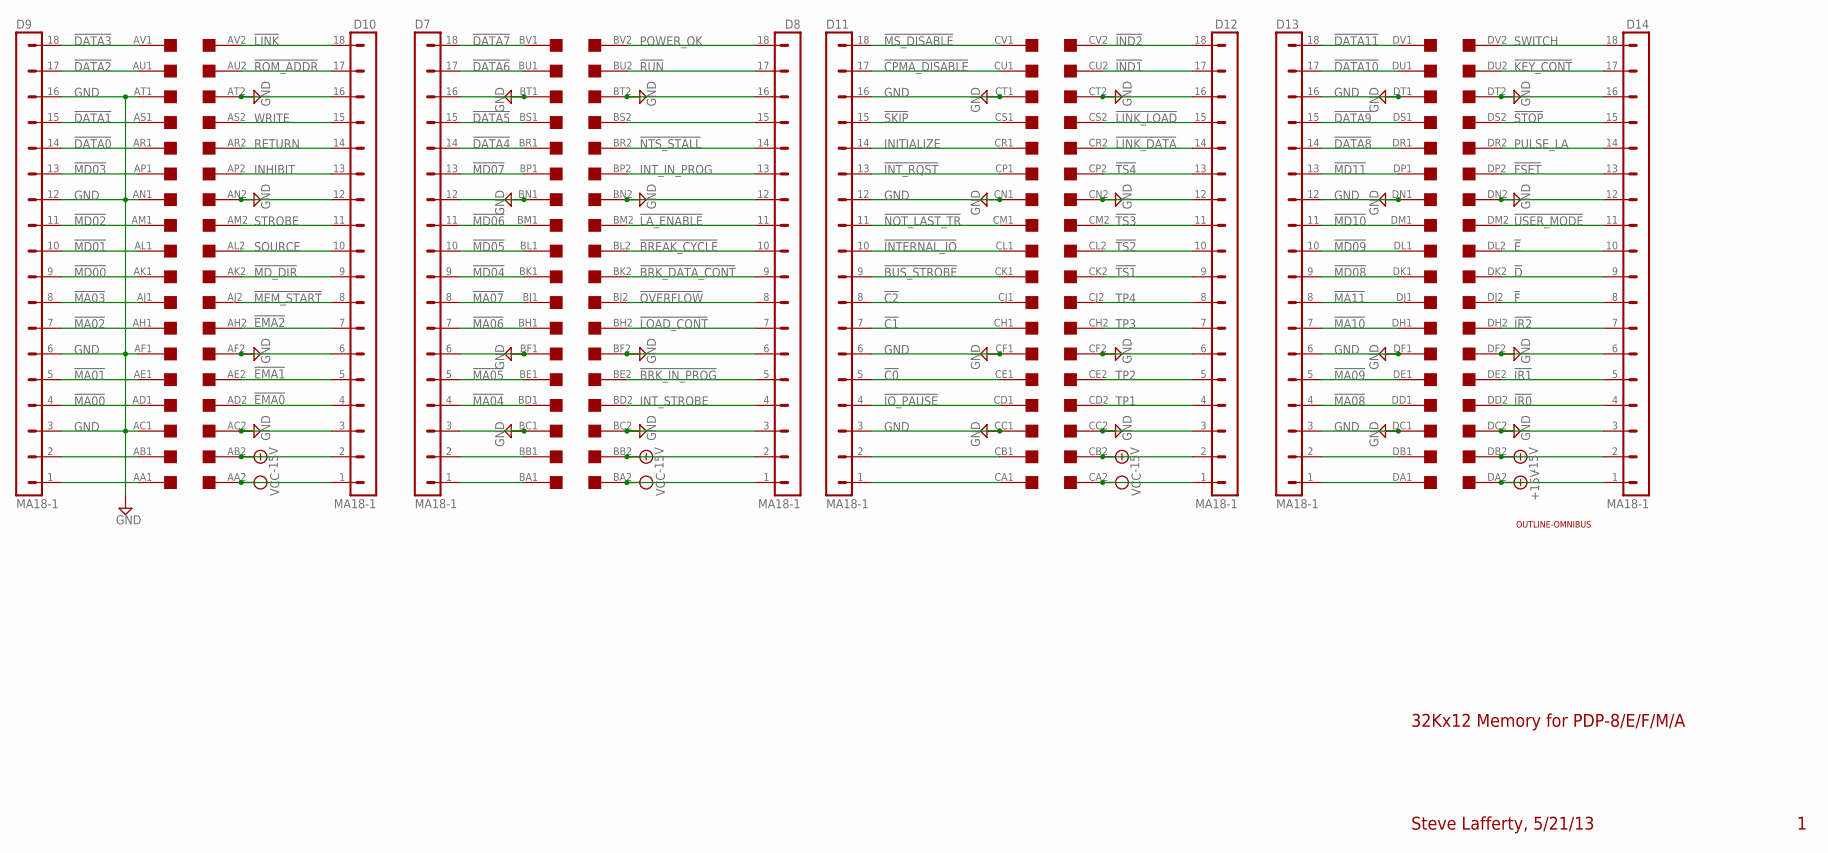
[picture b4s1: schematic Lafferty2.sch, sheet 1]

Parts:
D7, D8, D9, D10, D11, D12, D13, D14: MA18-1
U$1: OUTLINE-OMNIBUS; OMNIBUS
U$2: QUAD; EDGE-CON8

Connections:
!BREAK_CYCLE: D8.10, U$2.BL2
!BRK_DATA_CONT: D8.9, U$2.BK2
!BRK_IN_PROG: D8.5, U$2.BE2
!BUS_STROBE: D11.9, U$2.CK1
!C0: D11.5, U$2.CE1
!C1: D11.7, U$2.CH1
!C2: D11.8, U$2.CJ1
!CPMA_DISABLE: D11.17, U$2.CU1
!D: D14.9, U$2.DK2
!DATA0: D9.14, U$2.AR1
!DATA1: D9.15, U$2.AS1
!DATA2: D9.17, U$2.AU1
!DATA3: D9.18, U$2.AV1
!DATA4: D7.14, U$2.BR1
!DATA5: D7.15, U$2.BS1
!DATA6: D7.17, U$2.BU1
!DATA7: D7.18, U$2.BV1
!DATA8: D13.14, U$2.DR1
!DATA9: D13.15, U$2.DS1
!DATA10: D13.17, U$2.DU1
!DATA11: D13.18, U$2.DV1
!E: D14.10, U$2.DL2
!EMA0: D10.4, U$2.AD2; also elsewhere on the board
!EMA1: D10.5, U$2.AE2; also elsewhere on the board
!EMA2: D10.7, U$2.AH2; also elsewhere on the board
!F: D14.8, U$2.DJ2
!FSET: D14.13, U$2.DP2
!IND1: D12.17, U$2.CU2
!IND2: D12.18, U$2.CV2
!INTERNAL_IO: D11.10, U$2.CL1
!INT_RQST: D11.13, U$2.CP1
!IO_PAUSE: D11.4, U$2.CD1
!IR0: D14.4, U$2.DD2
!IR1: D14.5, U$2.DE2
!IR2: D14.7, U$2.DH2
!KEY_CONT: D14.17, U$2.DU2
!LA_ENABLE: D8.11, U$2.BM2
!LINK: D10.18, U$2.AV2
!LINK_DATA: D12.14, U$2.CR2
!LINK_LOAD: D12.15, U$2.CS2
!LOAD_CONT: D8.7, U$2.BH2
!MA00: D9.4, U$2.AD1; also elsewhere on the board
!MA01: D9.5, U$2.AE1; also elsewhere on the board
!MA02: D9.7, U$2.AH1; also elsewhere on the board
!MA03: D9.8, U$2.AJ1; also elsewhere on the board
!MA04: D7.4, U$2.BD1; also elsewhere on the board
!MA05: D7.5, U$2.BE1; also elsewhere on the board
!MA06: D7.7, U$2.BH1; also elsewhere on the board
!MA07: D7.8, U$2.BJ1; also elsewhere on the board
!MA08: D13.4, U$2.DD1; also elsewhere on the board
!MA09: D13.5, U$2.DE1; also elsewhere on the board
!MA10: D13.7, U$2.DH1; also elsewhere on the board
!MA11: D13.8, U$2.DJ1; also elsewhere on the board
!MD00: D9.9, U$2.AK1; also elsewhere on the board
!MD01: D9.10, U$2.AL1; also elsewhere on the board
!MD02: D9.11, U$2.AM1; also elsewhere on the board
!MD03: D9.13, U$2.AP1; also elsewhere on the board
!MD04: D7.9, U$2.BK1; also elsewhere on the board
!MD05: D7.10, U$2.BL1; also elsewhere on the board
!MD06: D7.11, U$2.BM1; also elsewhere on the board
!MD07: D7.13, U$2.BP1; also elsewhere on the board
!MD08: D13.9, U$2.DK1; also elsewhere on the board
!MD09: D13.10, U$2.DL1; also elsewhere on the board
!MD10: D13.11, U$2.DM1; also elsewhere on the board
!MD11: D13.13, U$2.DP1; also elsewhere on the board
!MD_DIR: D10.9, U$2.AK2; also elsewhere on the board
!MEM_START: D10.8, U$2.AJ2
!MS_DISABLE: D11.18, U$2.CV1
!NOT_LAST_TR: D11.11, U$2.CM1
!NTS_STALL: D8.14, U$2.BR2
!OVERFLOW: D8.8, U$2.BJ2
!ROM_ADDR: D10.17, U$2.AU2; also elsewhere on the board
!RUN: D8.17, U$2.BU2
!SKIP: D11.15, U$2.CS1
!STOP: D14.15, U$2.DS2
!TS1: D12.9, U$2.CK2
!TS2: D12.10, U$2.CL2
!TS3: D12.11, U$2.CM2
!TS4: D12.13, U$2.CP2
!USER_MODE: D14.11, U$2.DM2
+15V: D14.1, U$2.DA2
-15V: D8.2, D10.2, D12.2, D14.2, U$2.AB2, U$2.BB2, U$2.CB2, U$2.DB2
GND: D7.3, D7.6, D7.12, D7.16, D8.3, D8.6, D8.12, D8.16, D9.3, D9.6, D9.12, D9.16, D10.3, D10.6, D10.12, D10.16, D11.3, D11.6, D11.12, D11.16, D12.3, D12.6, D12.12, D12.16, D13.3, D13.6, D13.12, D13.16, D14.3, D14.6, D14.12, D14.16, U$2.AC1, U$2.AC2, U$2.AF1, U$2.AF2, U$2.AN1, U$2.AN2, U$2.AT1, U$2.AT2, U$2.BC1, U$2.BC2, U$2.BF1, U$2.BF2, U$2.BN1, U$2.BN2, U$2.BT1, U$2.BT2, U$2.CC1, U$2.CC2, U$2.CF1, U$2.CF2, U$2.CN1, U$2.CN2, U$2.CT1, U$2.CT2, U$2.DC1, U$2.DC2, U$2.DF1, U$2.DF2, U$2.DN1, U$2.DN2, U$2.DT1, U$2.DT2; also elsewhere on the board
INHIBIT: D10.13, U$2.AP2
INITIALIZE: D11.14, U$2.CR1
INT_IN_PROG: D8.13, U$2.BP2
INT_STROBE: D8.4, U$2.BD2
unnamed: D9.2, U$2.AB1
unnamed: D9.1, U$2.AA1
unnamed: D7.2, U$2.BB1
unnamed: D7.1, U$2.BA1
unnamed: D11.1, U$2.CA1
unnamed: D8.15, U$2.BS2
unnamed: D11.2, U$2.CB1
unnamed: D13.1, U$2.DA1
unnamed: D13.2, U$2.DB1
POWER_OK: D8.18, U$2.BV2; also elsewhere on the board
PULSE_LA: D14.14, U$2.DR2
RETURN: D10.14, U$2.AR2
SOURCE: D10.10, U$2.AL2; also elsewhere on the board
STROBE: D10.11, U$2.AM2
SWITCH: D14.18, U$2.DV2
TP1: D12.4, U$2.CD2
TP2: D12.5, U$2.CE2
TP3: D12.7, U$2.CH2
TP4: D12.8, U$2.CJ2
VCC: D8.1, D10.1, D12.1, U$2.AA2, U$2.BA2, U$2.CA2; also elsewhere on the board
WRITE: D10.15, U$2.AS2; also elsewhere on the board

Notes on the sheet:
32Kx12 Memory for PDP-8/E/F/M/A
Steve Lafferty, 5/21/13
